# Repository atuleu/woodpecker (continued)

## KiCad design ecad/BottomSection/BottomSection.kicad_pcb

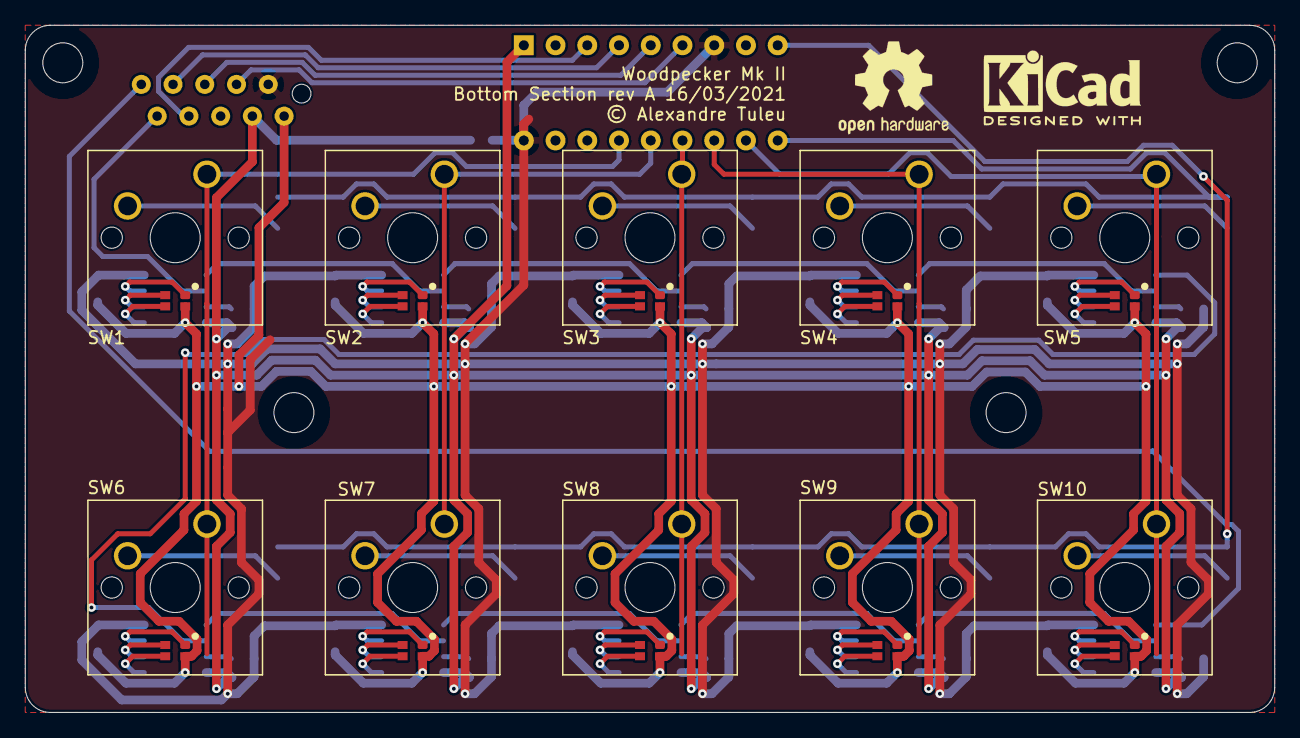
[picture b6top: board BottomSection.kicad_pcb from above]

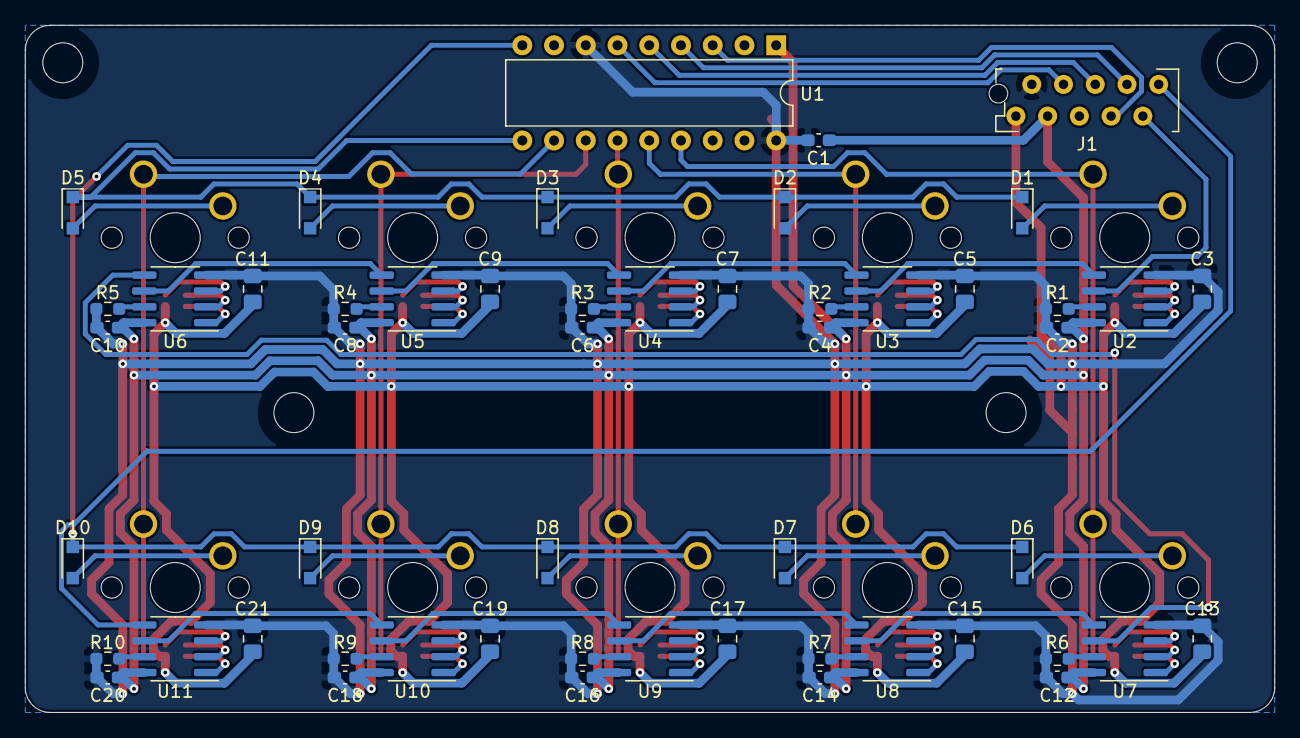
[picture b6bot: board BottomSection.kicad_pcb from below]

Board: 2 copper layers, 100.0 x 55.0 mm, 67 parts (53 on the bottom side), 75 nets.

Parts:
C1, C2, C4, C6, C8, C10, C12, C14, C16, C18, C20: 100nF; C_0603_1608Metric_Pad1.08x0.95mm_HandSolder
C3, C5, C7, C9, C11, C13, C15, C17, C19, C21: 2.2uF; C_0805_2012Metric_Pad1.18x1.45mm_HandSolder
D1, D2, D3, D4, D5, D6, D7, D8, D9, D10: 1N4148WS; D_SOD-323_HandSoldering
H1, H2, H3, H4: MountingHole; MountingHole_3.2mm_M3_DIN965
J1: Conn_02x05_Odd_Even; ConnectorMicromatch-10
R1, R2, R3, R4, R5, R6, R7, R8, R9, R10: 10.5K; R_0603_1608Metric_Pad0.98x0.95mm_HandSolder
SW1, SW2, SW3, SW4, SW5, SW6, SW7, SW8, SW9, SW10: Cherry_MX_LED; SW_Cherry_MX_1.00u_PCB_SMD_LED
U1: MCP23S09-xP; DIP-18_W7.62mm
U2, U3, U4, U5, U6, U7, U8, U9, U10, U11: TLC5973; SOIC-8_3.9x4.9mm_P1.27mm

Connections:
+3V3: C1.1, C2.1, C4.1, C6.1, C8.1, C10.1, C12.1, C14.1, C16.1, C18.1, C20.1, J1.3, U1.1, U2.8, U3.8, U4.8, U5.8, U6.8, U7.8, U8.8, U9.8, U10.8, U11.8
/C1: SW1.5, SW6.5, U1.15
/C2: SW2.5, SW7.5, U1.14
/C3: SW3.5, SW8.5, U1.13
/C4: SW4.5, SW9.5, U1.12
/C5: SW5.5, SW10.5, U1.11
/DI: J1.9, U2.6
/DO: J1.10, U11.5
/MISO: J1.4, U1.6
/MOSI: J1.6, U1.5
/MX_2/DI: U2.5, U3.6
/MX_3/DI: U3.5, U4.6
/MX_4/DI: U4.5, U5.6
/MX_5/DI: U5.5, U6.6
/MX_6/DI: U6.5, U7.6
/MX_7/DI: U7.5, U8.6
/MX_8/DI: U8.5, U9.6
/MX_9/DI: U9.5, U10.6
/MX_10/DI: U10.5, U11.6
/R1: D1.1, D2.1, D3.1, D4.1, D5.1, U1.10
/R2: D6.1, D7.1, D8.1, D9.1, D10.1, U1.9
/SCK: J1.8, U1.4
/~CS_ROW: J1.7, U1.3
GND: C1.2, C2.2, C3.2, C4.2, C5.2, C6.2, C7.2, C8.2, C9.2, C10.2, C11.2, C12.2, C13.2, C14.2, C15.2, C16.2, C17.2, C18.2, C19.2, C20.2, C21.2, J1.2, R1.2, R2.2, R3.2, R4.2, R5.2, R6.2, R7.2, R8.2, R9.2, R10.2, U1.7, U1.18, U2.4, U3.4, U4.4, U5.4, U6.4, U7.4, U8.4, U9.4, U10.4, U11.4
unnamed: D1.2, SW1.6
unnamed: D2.2, SW2.6
unnamed: D3.2, SW3.6
unnamed: D4.2, SW4.6
unnamed: D5.2, SW5.6
unnamed: D6.2, SW6.6
unnamed: D7.2, SW7.6
unnamed: D8.2, SW8.6
unnamed: D9.2, SW9.6
unnamed: D10.2, SW10.6
unnamed: R1.1, U2.7
unnamed: R2.1, U3.7
unnamed: R3.1, U4.7
unnamed: R4.1, U5.7
unnamed: R5.1, U6.7
unnamed: R6.1, U7.7
unnamed: R7.1, U8.7
unnamed: R8.1, U9.7
unnamed: R9.1, U10.7
unnamed: R10.1, U11.7
unnamed: SW1.1, U2.3
unnamed: SW1.2, U2.2
unnamed: SW1.4, U2.1
unnamed: SW2.1, U3.3
unnamed: SW2.2, U3.2
unnamed: SW2.4, U3.1
unnamed: SW3.1, U4.3
unnamed: SW3.2, U4.2
unnamed: SW3.4, U4.1
unnamed: SW4.1, U5.3
unnamed: SW4.2, U5.2
unnamed: SW4.4, U5.1
unnamed: SW5.1, U6.3
unnamed: SW5.2, U6.2
unnamed: SW5.4, U6.1
unnamed: SW6.1, U7.3
unnamed: SW6.2, U7.2
unnamed: SW6.4, U7.1
unnamed: SW7.1, U8.3
unnamed: SW7.2, U8.2
unnamed: SW7.4, U8.1
unnamed: SW8.1, U9.3
unnamed: SW8.2, U9.2
unnamed: SW8.4, U9.1
unnamed: SW9.1, U10.3
unnamed: SW9.2, U10.2
unnamed: SW9.4, U10.1
unnamed: SW10.1, U11.3
unnamed: SW10.2, U11.2
unnamed: SW10.4, U11.1
VLED: C3.1, C5.1, C7.1, C9.1, C11.1, C13.1, C15.1, C17.1, C19.1, C21.1, J1.1, SW1.3, SW2.3, SW3.3, SW4.3, SW5.3, SW6.3, SW7.3, SW8.3, SW9.3, SW10.3

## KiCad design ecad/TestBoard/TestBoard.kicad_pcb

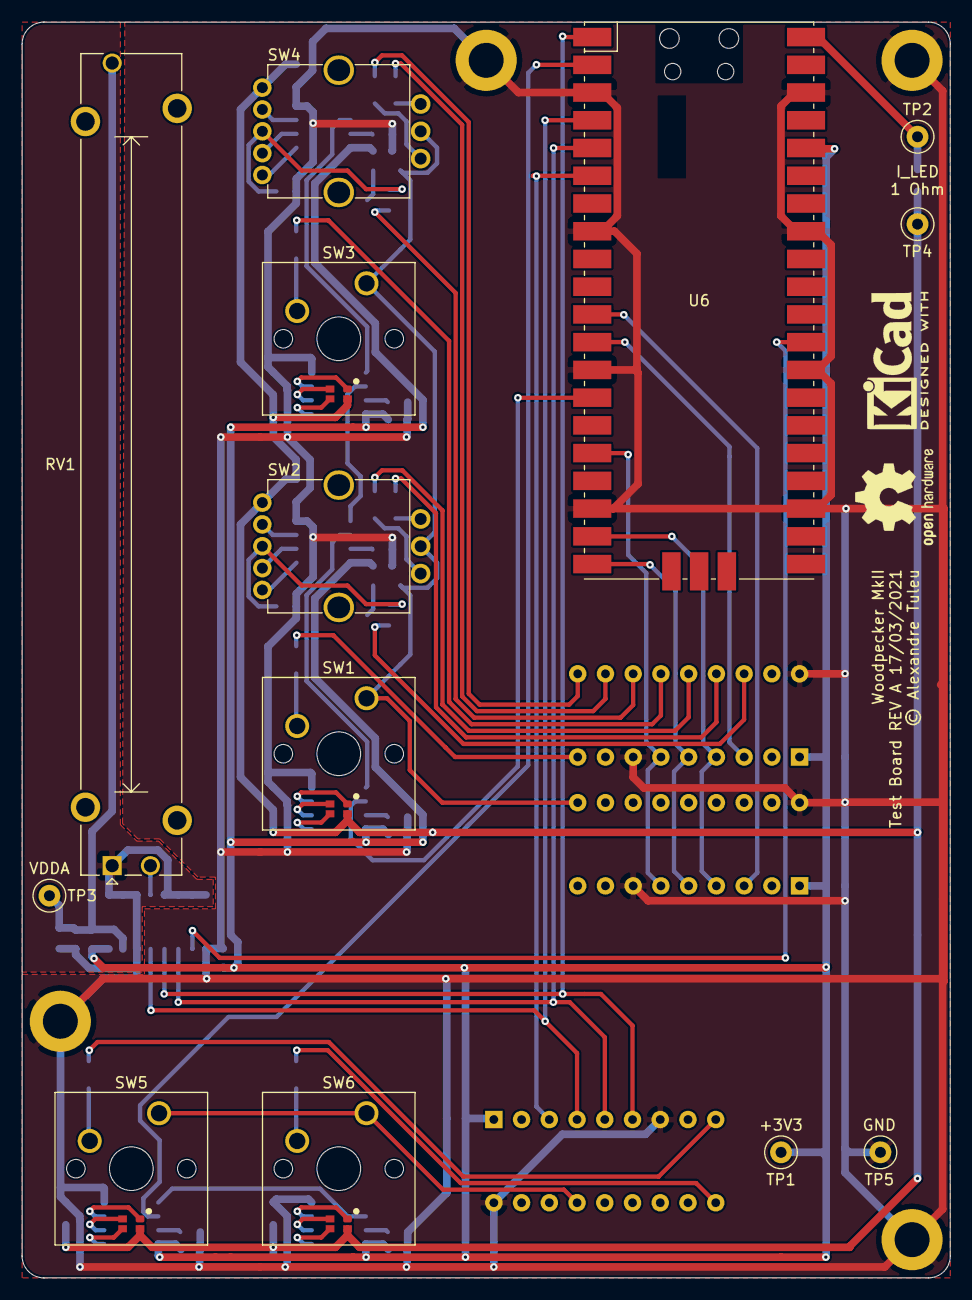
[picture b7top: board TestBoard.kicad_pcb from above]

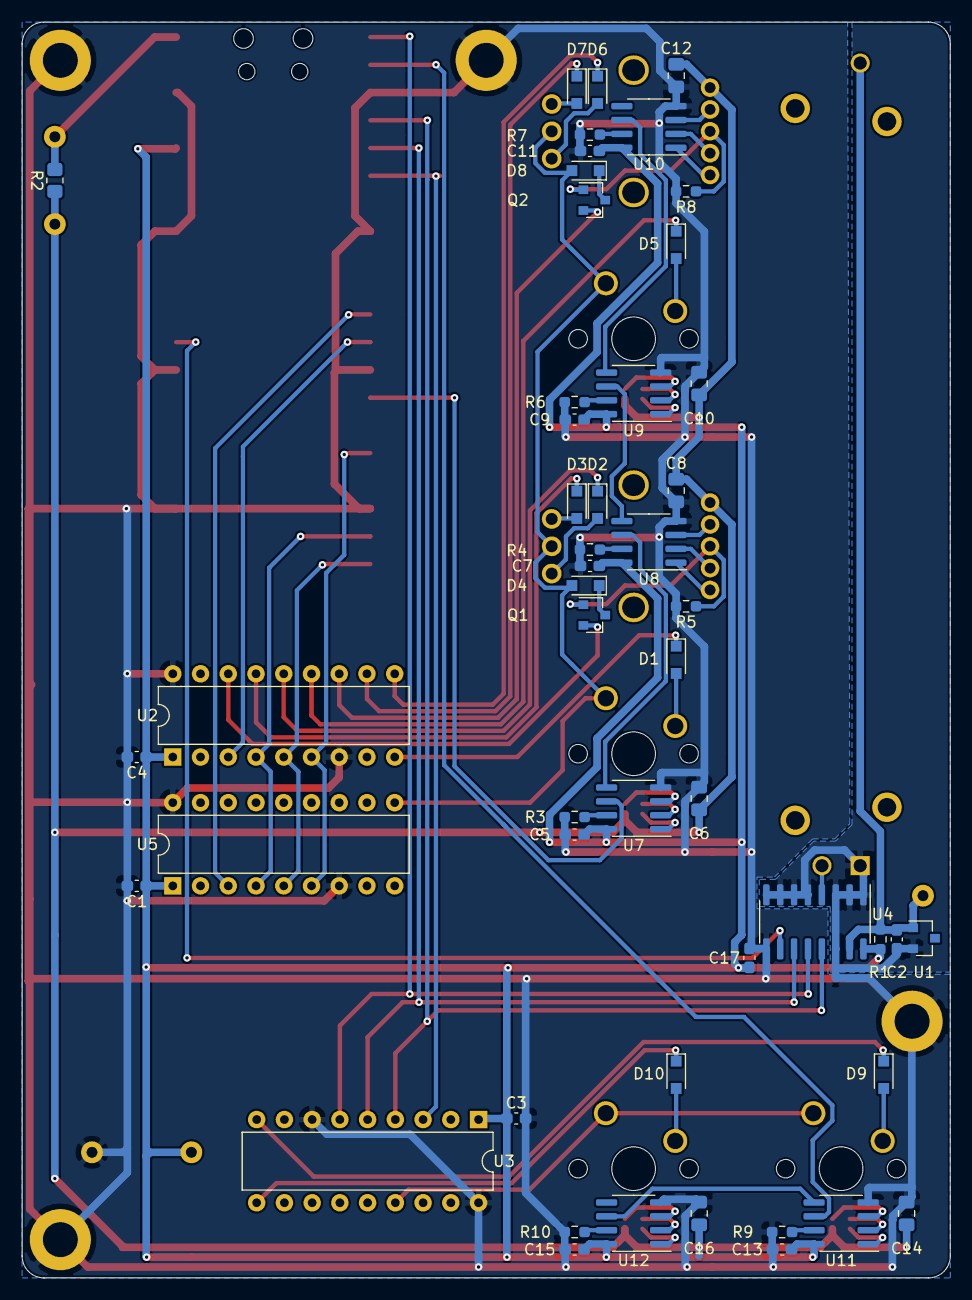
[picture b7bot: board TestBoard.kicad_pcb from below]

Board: 2 copper layers, 85.0 x 115.0 mm, 64 parts (51 on the bottom side), 71 nets.

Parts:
C1, C2, C3, C4, C5, C7, C9, C11, C13, C15, C17: 100nF; C_0603_1608Metric_Pad1.08x0.95mm_HandSolder
C6, C8, C10, C12, C14, C16: 2.2uF; C_0805_2012Metric_Pad1.18x1.45mm_HandSolder
D1, D2, D3, D4, D5, D6, D7, D8, D9, D10: 1N4148WS; D_SOD-323_HandSoldering
JP1: Jumper; jumper_0_4
Q1, Q2: BSS138; SOT-23
R1: 43R; R_0603_1608Metric_Pad0.98x0.95mm_HandSolder
R2: 1, 1/4W; R_0805_2012Metric_Pad1.20x1.40mm_HandSolder
R3, R4, R6, R7, R9, R10: 10.5K; R_0603_1608Metric_Pad0.98x0.95mm_HandSolder
R5, R8: 10K; R_0603_1608Metric_Pad0.98x0.95mm_HandSolder
RV1: R_POT; Potentiometer_Bourns_PTA6043_Single_Slide
SW1, SW3, SW5, SW6: Cherry_MX_LED; SW_Cherry_MX_1.00u_PCB_SMD_LED
SW2, SW4: PEL12T; PEL12T-4xxxS-S1024
TP1: 3V3; TestPoint_Loop_D2.50mm_Drill1.0mm_LowProfile
TP2: VBUS; TestPoint_Loop_D2.50mm_Drill1.0mm_LowProfile
TP3: VDDA; TestPoint_Loop_D2.50mm_Drill1.0mm_LowProfile
TP4: VLED; TestPoint_Loop_D2.50mm_Drill1.0mm_LowProfile
TP5: GND; TestPoint_Loop_D2.50mm_Drill1.0mm_LowProfile
U1: LM4040DBZ-3; SOT-23
U2, U3, U5: MCP23S09-xP; DIP-18_W7.62mm
U4: MCP3008; SOIC-16_3.9x9.9mm_P1.27mm
U6: RPI_Pico; RPi_Pico_SMD
U7, U8, U9, U10, U11, U12: TLC5973; SOIC-8_3.9x4.9mm_P1.27mm

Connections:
+3V3: C1.1, C3.1, C4.1, C5.1, C7.1, C9.1, C11.1, C13.1, C15.1, C17.1, R1.1, TP1.1, U2.1, U3.1, U4.16, U5.1, U6.36, U7.8, U8.8, U9.8, U10.8, U11.8, U12.8
/BOT_C_DI: U6.2, U11.6
/BOT_MISO: U3.6, U4.12, U6.1
/BOT_MOSI: U3.5, U4.11, U6.5
/BOT_SCK: U3.4, U4.13, U6.4
/CBOT: SW5.5, SW6.5, U3.15
/CTOP: D4.2, D8.2, SW1.5, SW2.C, SW3.5, SW4.C, U5.10
/PT1: RV1.2, U4.4
/QA1: D6.1, U2.10
/QA2: D2.1, U2.14
/QB1: D7.1, U2.11
/QB2: D3.1, U2.15
/R1: Q2.2, U2.12
/R2: D5.1, U2.13
/R3: Q1.2, U2.16
/R4: D1.1, U2.9
/R5: D9.1, U3.9
/R6: D10.1, U3.10
/Sheet60629BEB/DI: U9.5, U10.6
/Sheet60634508/DI: U8.5, U9.6
/TOP_C_DI: U6.14, U7.6
/TOP_MISO: U2.6, U5.6, U6.16
/TOP_MOSI: U2.5, U5.5, U6.20
/TOP_SCK: U2.4, U5.4, U6.19
/sheet607AC642/DI: U11.5, U12.6
/sheet60638B8E/DI: U7.5, U8.6
/~CS_ADC_C: U4.10, U6.29
/~CS_COL_C: U5.3, U6.11
/~CS_MX_C: U3.3, U6.6
/~CS_ROW_C: U2.3, U6.12
GND: C1.2, C3.2, C4.2, C5.2, C6.2, C7.2, C8.2, C9.2, C10.2, C11.2, C12.2, C13.2, C14.2, C15.2, C16.2, C17.2, JP1.2, R3.2, R4.2, R5.2, R6.2, R7.2, R8.2, R9.2, R10.2, TP5.1, U2.7, U2.18, U3.7, U3.18, U4.9, U5.7, U5.18, U6.3, U6.8, U6.13, U6.18, U6.23, U6.28, U6.33, U6.38, U7.4, U8.4, U9.4, U10.4, U11.4, U12.4
GND1: C2.2, JP1.1, RV1.1, U1.2, U4.1, U4.2, U4.3, U4.5, U4.6, U4.7, U4.8, U4.14
unnamed: D1.2, SW1.6
unnamed: D2.2, SW2.A
unnamed: D3.2, SW2.B
unnamed: D4.1, Q1.3
unnamed: D5.2, SW3.6
unnamed: D6.2, SW4.A
unnamed: D7.2, SW4.B
unnamed: D8.1, Q2.3
unnamed: D9.2, SW5.6
unnamed: D10.2, SW6.6
unnamed: Q1.1, R5.1, SW2.3
unnamed: Q2.1, R8.1, SW4.3
unnamed: R3.1, U7.7
unnamed: R4.1, U8.7
unnamed: R6.1, U9.7
unnamed: R7.1, U10.7
unnamed: R9.1, U11.7
unnamed: R10.1, U12.7
unnamed: SW1.1, U7.3
unnamed: SW1.2, U7.2
unnamed: SW1.4, U7.1
unnamed: SW2.1, U8.1
unnamed: SW2.2, U8.2
unnamed: SW2.4, U8.3
unnamed: SW3.1, U9.3
unnamed: SW3.2, U9.2
unnamed: SW3.4, U9.1
unnamed: SW4.1, U10.1
unnamed: SW4.2, U10.2
unnamed: SW4.4, U10.3
unnamed: SW5.1, U11.3
unnamed: SW5.2, U11.2
unnamed: SW5.4, U11.1
unnamed: SW6.1, U12.3
unnamed: SW6.2, U12.2
unnamed: SW6.4, U12.1
VBUS: R2.2, TP2.1, U6.40
VDDA: C2.1, R1.2, RV1.3, TP3.1, U1.1, U4.15
VLED: C6.1, C8.1, C10.1, C12.1, C14.1, C16.1, R2.1, SW1.3, SW2.5, SW3.3, SW4.5, SW5.3, SW6.3, TP4.1

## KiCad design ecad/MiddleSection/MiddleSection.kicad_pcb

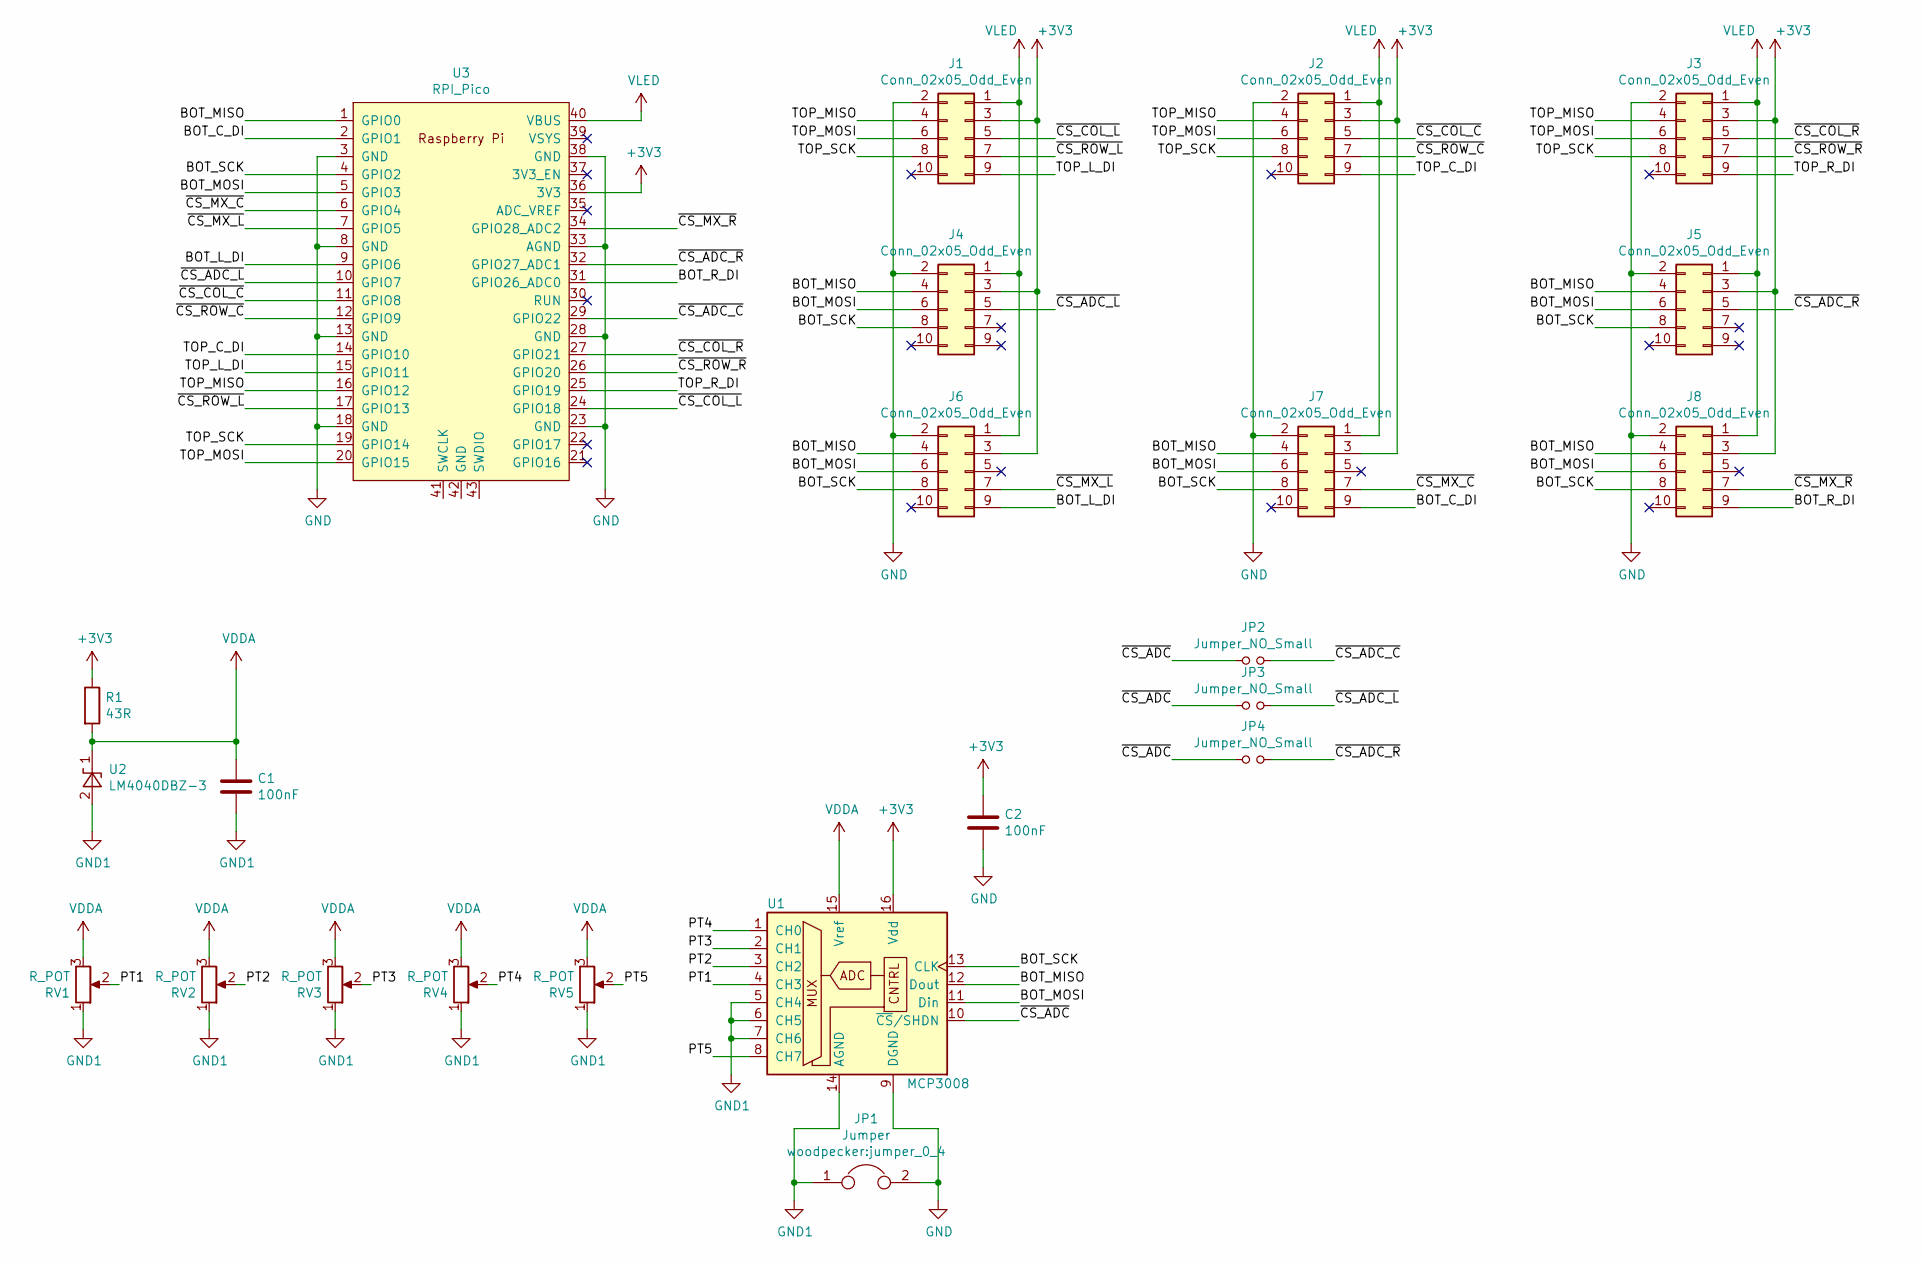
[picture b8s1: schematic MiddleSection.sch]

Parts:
C1, C2: 100nF; C_0603_1608Metric_Pad1.08x0.95mm_HandSolder
J1, J2, J3, J4, J5, J6, J7, J8: Conn_02x05_Odd_Even; ConnectorMicromatch-10
JP1: Jumper; jumper_0_4
JP2, JP3, JP4: Jumper_NO_Small; SolderJumper-2_P1.3mm_Open_RoundedPad1.0x1.5mm
R1: 43R; R_0603_1608Metric_Pad0.98x0.95mm_HandSolder
RV1, RV2, RV3, RV4, RV5: R_POT; Potentiometer_Bourns_PTA6043_Single_Slide
U1: MCP3008; SOIC-16_3.9x9.9mm_P1.27mm
U2: LM4040DBZ-3; SOT-23
U3: RPI_Pico; RPi_Pico_SMD_TH

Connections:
+3V3: C2.1, J1.3, J2.3, J3.3, J4.3, J5.3, J6.3, J7.3, J8.3, R1.1, U1.16 (Vdd), U3.36 (3V3)
/BOT_C_DI: J7.9, U3.2 (GPIO1)
/BOT_L_DI: J6.9, U3.9 (GPIO6)
/BOT_MISO: J4.4, J5.4, J6.4, J7.4, J8.4, U1.12 (Dout), U3.1 (GPIO0)
/BOT_MOSI: J4.6, J5.6, J6.6, J7.6, J8.6, U1.11 (Din), U3.5 (GPIO3)
/BOT_R_DI: J8.9, U3.31 (GPIO26_ADC0)
/BOT_SCK: J4.8, J5.8, J6.8, J7.8, J8.8, U1.13 (CLK), U3.4 (GPIO2)
/PT1: RV1.2, U1.4 (CH3)
/PT2: RV2.2, U1.3 (CH2)
/PT3: RV3.2, U1.2 (CH1)
/PT4: RV4.2, U1.1 (CH0)
/PT5: RV5.2, U1.8 (CH7)
/TOP_C_DI: J2.9, U3.14 (GPIO10)
/TOP_L_DI: J1.9, U3.15 (GPIO11)
/TOP_MISO: J1.4, J2.4, J3.4, U3.16 (GPIO12)
/TOP_MOSI: J1.6, J2.6, J3.6, U3.20 (GPIO15)
/TOP_R_DI: J3.9, U3.25 (GPIO19)
/TOP_SCK: J1.8, J2.8, J3.8, U3.19 (GPIO14)
/~CS_ADC: JP2.1, JP3.1, JP4.1, U1.10 (~CS~/SHDN)
/~CS_ADC_C: JP2.2, U3.29 (GPIO22)
/~CS_ADC_L: J4.5, JP3.2, U3.10 (GPIO7)
/~CS_ADC_R: J5.5, JP4.2, U3.32 (GPIO27_ADC1)
/~CS_COL_C: J2.5, U3.11 (GPIO8)
/~CS_COL_L: J1.5, U3.24 (GPIO18)
/~CS_COL_R: J3.5, U3.27 (GPIO21)
/~CS_MX_C: J7.7, U3.6 (GPIO4)
/~CS_MX_L: J6.7, U3.7 (GPIO5)
/~CS_MX_R: J8.7, U3.34 (GPIO28_ADC2)
/~CS_ROW_C: J2.7, U3.12 (GPIO9)
/~CS_ROW_L: J1.7, U3.17 (GPIO13)
/~CS_ROW_R: J3.7, U3.26 (GPIO20)
GND: C2.2, J1.2, J2.2, J3.2, J4.2, J5.2, J6.2, J7.2, J8.2, JP1.2, U1.9 (DGND), U3.3 (GND), U3.8 (GND), U3.13 (GND), U3.18 (GND), U3.23 (GND), U3.28 (GND), U3.33 (AGND), U3.38 (GND)
GND1: C1.2, JP1.1, RV1.1, RV2.1, RV3.1, RV4.1, RV5.1, U1.5 (CH4), U1.6 (CH5), U1.7 (CH6), U1.14 (AGND), U2.2 (A)
VDDA: C1.1, R1.2, RV1.3, RV2.3, RV3.3, RV4.3, RV5.3, U1.15 (Vref), U2.1 (K)
VLED: J1.1, J2.1, J3.1, J4.1, J5.1, J6.1, J7.1, J8.1, U3.40 (VBUS)

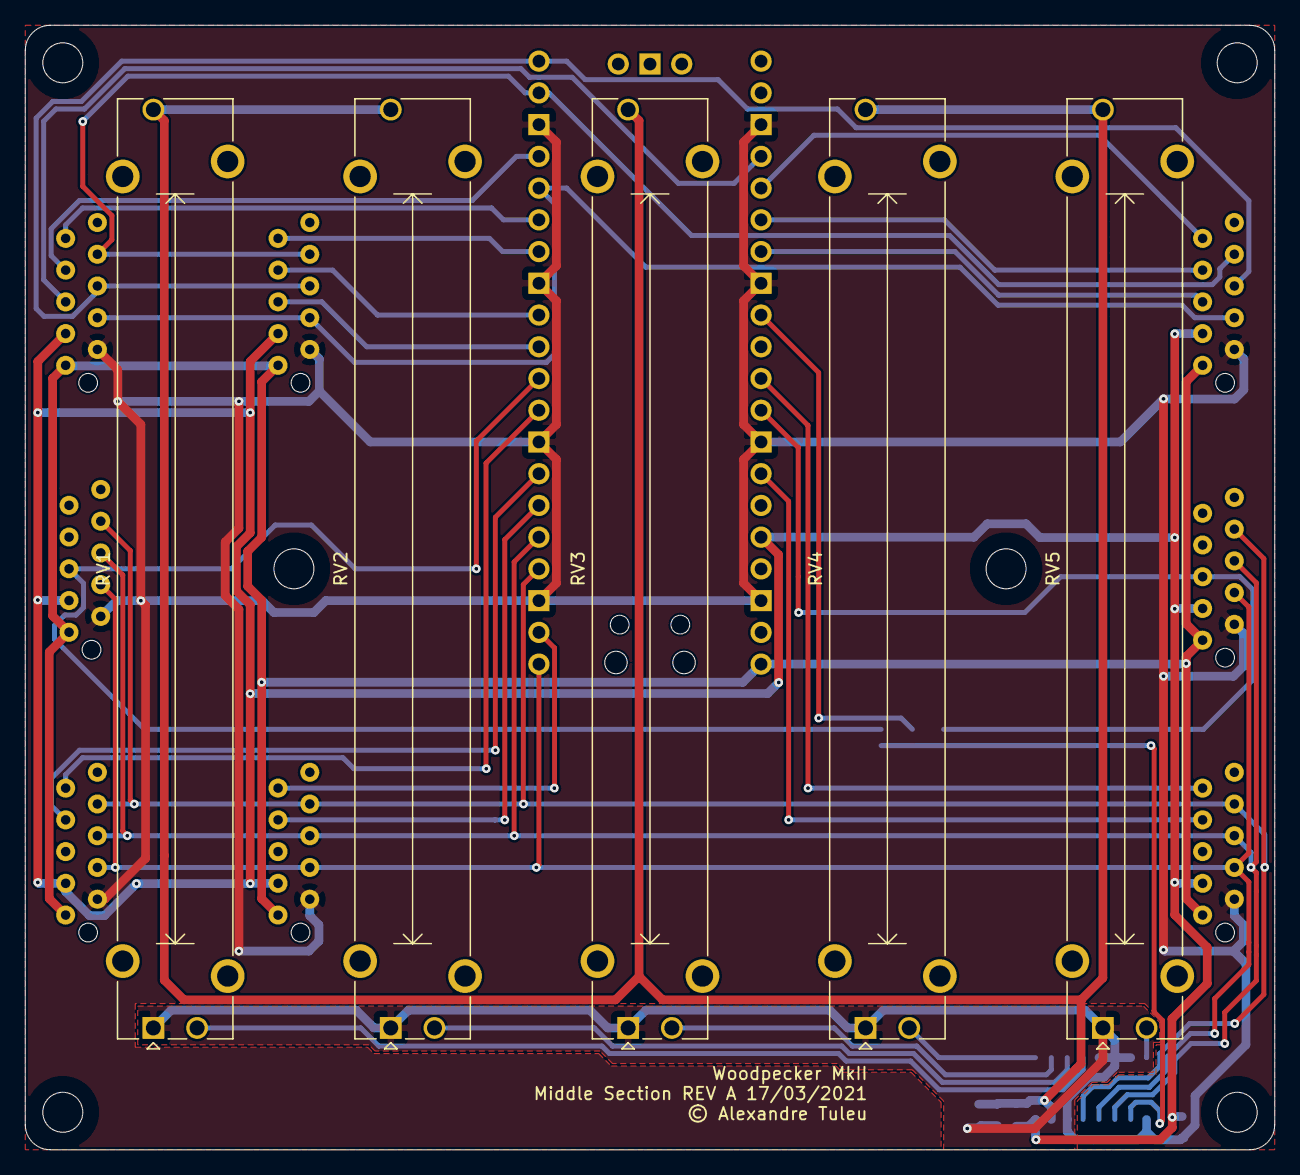
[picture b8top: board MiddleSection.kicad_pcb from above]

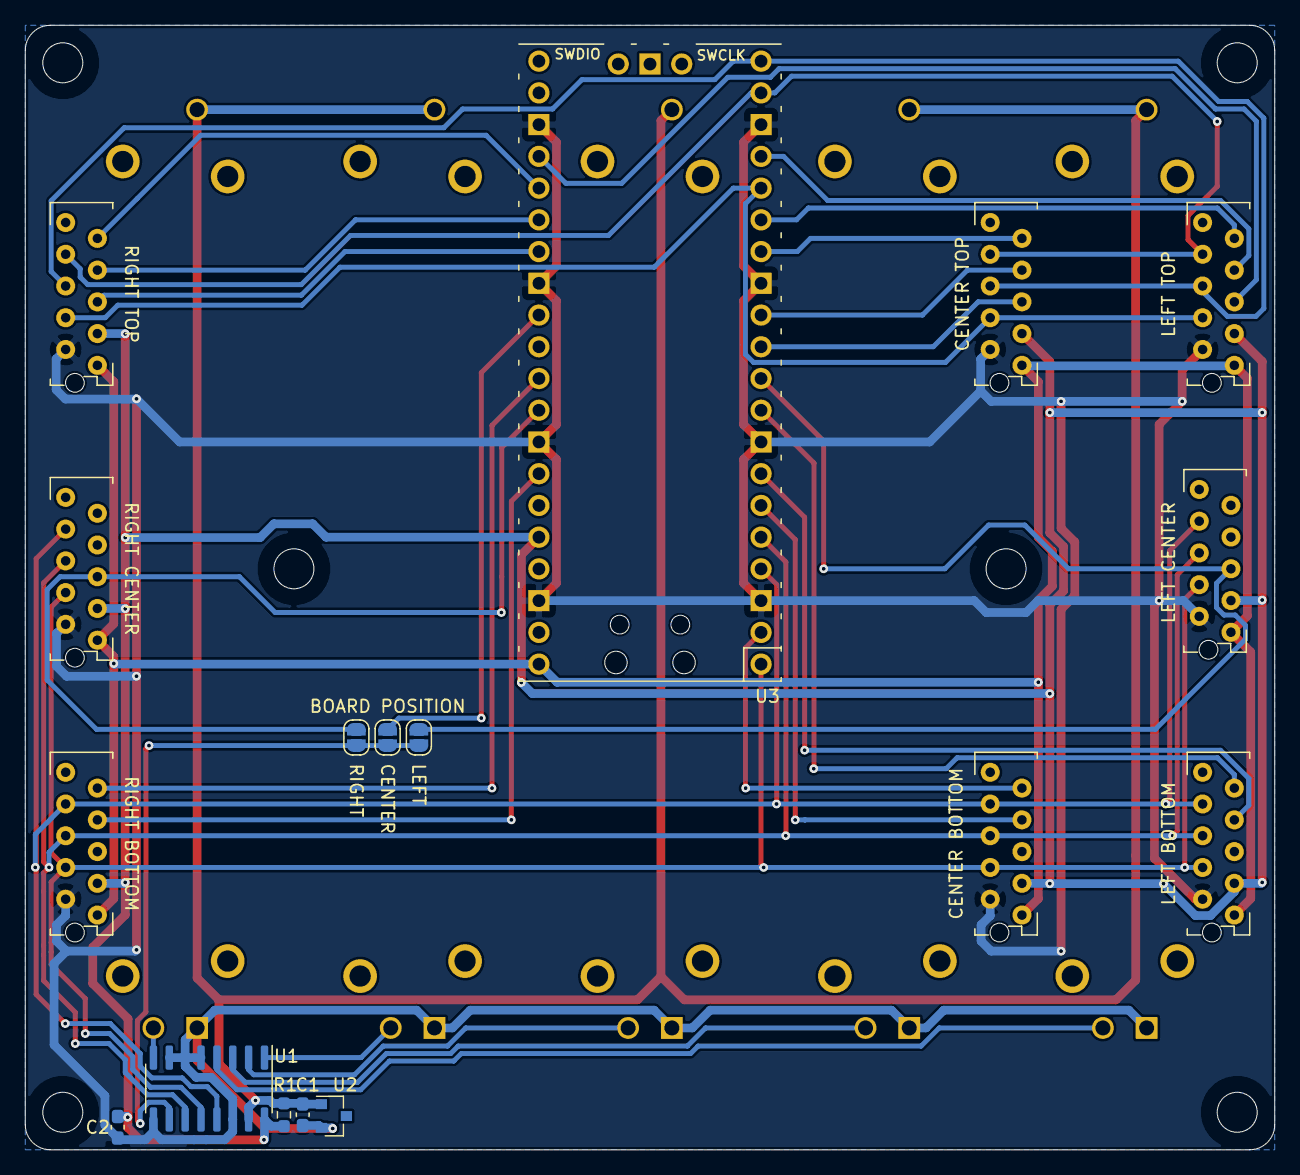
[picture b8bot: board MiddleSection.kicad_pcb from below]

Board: 2 copper layers, 100.0 x 90.0 mm, 23 parts (18 on the bottom side), 35 nets.

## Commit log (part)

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2021-03-12 layouts a top section
2021-03-13 Adds bottom section in monolithic design
2021-03-13 Corrects Quadrature encoder debounce circuit on put them on the scan matrix
2021-03-16 Implemented Top Section Revision A
2021-03-16 Uses relative paths for libraries
2021-03-16 Layouts the bottom section
2021-03-17 Builds a middle section electronics
2021-03-28 Sets debug board
2021-03-28 Hello world program
2021-03-28 Displays clock
2021-03-29 Makes LED shine !
    Let the LED shine !
    Let the LED shine In !
2021-04-17 Refactors displays in own module
2021-04-17 Adds 8/12 bit color converter
2021-04-17 binary clock
2021-04-18 Symchronous poll upload of LED data
2022-03-13 [wip] keypress
2022-06-14 MX key drawing
2024-09-02 Starts (again) a top section board
    Hopefully the use of ws2812 like LED will help a lot.
2024-09-04 Draft a slightly smaller top board
2024-09-04 Adds a bottom section
2024-09-04 Adds a bottom_section board.
    It was fast. Seems the right design choices.
2024-09-10 Renames top_board to top_section
2024-09-10 Starts a middle_section
2024-09-10 [WIP]
2024-09-11 Adds a control board with a minimal USB-C RCPT
2024-09-12 Finishes up Middle Section
2024-09-12 Makes a control_board
2024-09-17 Updates boards
2025-08-27 Uses WS2811 led communication everywhere
2025-09-01 Uses Attiny1617 MCU for ADC & Matrix RO
2025-09-02 Uses attiny16176
2025-09-15 [WIP] Control board
2025-09-15 Changed layout for common libraries
2025-09-16 Layouted new control board
2025-09-16 Adds a first logo
2025-09-17 WIP LED
2025-09-18 [WIP] Layouting a matric led driver
2025-09-18 Uses a LP5864 LED Matrix Driver for Top Section
2025-09-18 Uses LED Matrix controller on all board.
    It simplifies so much the design for a small cost.
2025-09-18 Updated Controller for I2C controlled LED Matrices
2025-09-19 First production run for PCB
2025-09-22 Skeleton for a Attiny1617 firmware for sections.
2025-09-22 Stubs better program
2025-09-22 Adds crc8 and basic communication protocol support.
2025-09-23 Update frame setup.
2025-09-23 Makes an akward UART clock.
    It runs at 1000/1028 Hz.
2025-09-24 Makes the whole UART with interrupt.
2025-09-24 Got some tweeks from review with chatgpt.
2025-09-24 Sketches a middle section firmware to read fader and update buttons.
2025-09-25 Stubs a rp2040 firmware
2025-09-25 Working on compiling CDC + RDNIS / lwip stack
2025-09-25 Adds key logos from SVG
2025-09-25 Adds OpenOCD support.
2025-09-25 [firmware/controller] Finishes merging examples for httpd server.
2025-09-25 [firmware/controller] Add custom http content. need debugging.
2025-09-26 Improves netusb interface
2025-09-26 Draft an OSC service based on UDP transport.
    Implementation only partially follow the specs. No #BLOCK, No timetag, No
    multiple arg. But it should be sufficient.
2025-09-27 Outputs new step files
2025-10-01 Fixes slider
2025-10-01 Increase the number of timeout syspool.
    There was some error when plugging it. Maybe a race. It is better to increase it
    a bit.
2025-10-03 [wip][firmware/controller] Adds register map for LP5864
2025-10-04 [firmware] and color was !
2025-10-06 Draft an IRQ handler.
2025-10-06 DMA managed I2C bus.
    Maybe need to be made more robust to SDA stall.
2025-10-08 [firmware/controller]Shares DMA irqs.
2025-10-08 Adds a pio driven RX
    Code inspired by pico C sdk examples.
2025-10-08 [firmware/controller] Tracked down DMA noise from multiple chunks.
2025-10-08 Uses rainbow effect again.
2025-10-08 [firmware/controller] Uses a 1 chunk DMA upload.
    Two chunk transmission had some issue as incomplete transfer were
    triggered. This solves it.
2025-10-09 [firmware/controller] Tries to use I2C STOP detection.
2025-10-09 [firmware/controller] Disables interrupt on blocking write, use scheduled everywhere.
    Still need hard reboot on program;
2025-10-10 Marks ISR handler as such to avoid weird initialization problems.
    Also marks them not in flash.
2025-10-10 [firmware/daughters] Fixes UART encoding.
2025-10-10 Debugs top section
    * Makes sure the memory is initialized (added .rodata to the list of memory to
    upload).
    * Divide by two the number of pulse, we get two event per mechanical click.
    * Makes sure the state of the button are written to the frame.
2025-10-13 Measure the time the rendering takes.
2025-10-13 [firmware/controller] Tries to debug DMA channel.
    It is not working, It seems that I never have a decreasing count. Maybe I need
    ping-pong, Or maybe, I could go heavier on interrupt and not use a DMA approach.
2025-10-13 Changes the UART_Rx to a fixed packet size transfer.
    Simpler coding, better sync, no weird DMA math. Needs to be tested.
2025-10-14 [firmware/controller] iIntroduces ATOMIC_CORE_BLOCK macro
    to define a nice lock approach to interrupt disabling.
2025-10-14 [firmware/controller] Working I2C_DMA
2025-10-14 [firmware/controller] Fixes interrupts and dma handlers.
    But now I get garbage from the pio...
2025-10-14 [firmware/controller] Tweeks the PIO.
2025-10-14 [firmware/controller] Fixes the UART RX.
    Wrong offset, wrong CRC check.
    If all is fine, no RX errors.
2025-10-15 Refactors UART_Rx to section_rx
2025-10-15 Adds encoder struct and logic.
2025-10-15 Uses 4bit two complements values.
2025-10-15 Adds visual section.
2025-10-15 [firmware/controller] Puts all logic on core1
2025-10-16 [firmware/controller] Fixes visuals and hid.
2025-10-16 [firmware/controller] Prints event on stdout.
    Next steps: OSC transport.
2025-10-16 [firmware/daughter] Tweaks.
2025-10-16 [firmware/controller] section_rx deadlock fix.
    It was always checking the deadline. The infinity time tricks is wrong.
2025-10-16 [firmware/controller] Avoids long lockup on stdio
2025-10-16 [firmware/middle_section] Fixes fader readout and time differences computation.
    Learned about GCC int promotion in expressions.
2025-10-16 [firmware/controller] Filter out jitter changes in fader.
2025-10-16 [firmware/daughter] Improves debouncer and knobs
    * Uses different bounce time for push-button and knob.
    * Uses a different encoder starting value to avoid mis and multi trigger per detent.
2025-10-16 Ensure dma channel are aborted on failed TX.
    Otherwise the bus gets stuck!!!.
2025-10-16 Fixes visuals for 3 sections.
2025-10-16 Fixes encoder 4bit diff.
2025-10-16 Tweeks startup animation.
2025-10-16 [firmware/controller] Implements OSC message sending.
2025-10-16 Tweeks RGB color calibration.
    Still under the limit of 330mA at full output.
2025-10-22 [firmware/controller] Adds encoder update events.
2025-10-24 [firmware/controller] Implements color update from OSC.
